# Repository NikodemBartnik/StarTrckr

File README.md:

## StarTracker - 3 axis astrophotography tracking solution

**Project is still in development and it may change!**<br>
Welcome to the StarTrckr project, an innovative solution to the problem of tracking in astrophotography. The goal of this project is to get over the limits of conventional tracking techniques so that hobbyists and enthusiasts can more easily take beautiful pictures of the night sky. Additionaly this construction enables for easier tracking of other objects (for example satellites) but the feature is not implemented yet.

A further benefit of the design is that it can be completely 3D printed, making it simple for everyone to construct and modify their own tracking device. It is planned to design an additional pro version that features steel parts for increased stiffness of the construction but 3D printed version will always stay as the bassis thats accesible and easy to replicate for everyone.

Since he was a young child, Nikodem Bartnik, the project's creator, has been fascinated about observing the night sky and space in general.  He is constantly searching for new ways to enhance the system and make it easier to use for users of all levels. At the same time he is into developing various open source projects and documenting the journeys of creating them on his YouTube channel. Additionaly is a part of Silesian Aerospace Technologies science club where together with friends he develops high altitude balloons, rockets and cubesat subsystems.

Designed by [Nikodem Bartnik](https://www.youtube.com/nikodembartnik). 

## Mechanics
Different design approaches have been considered and in the end multiple designs were created. Some of those are presented in the image below.

Most parts have been 3D printed and only a few additional parts like bearings, screws and motors are neccesary from the mechanical point of view. As of writing this readme there are three versions included in cad folder (v2, v3 nad v4). At this point v3 is prefered version and the one that is currently tested. Following list of printed parts reffers to v3.
| Name                | Amount |
|----------------------|-------|
| arm1.3mf             | 1     |
| arm2.3mf             | 1     |
| arm3.3mf             | 1     |
| base_pcb_box.3mf     | 1     |
| base_motor_holder.3mf| 1     |
| base_gear.3mf        | 1     |
| base_bearing_cap.3mf | 1     |
| base_gear_small.3mf  | 1     |
| gt2_pulley.3mf       | 2     |
| shaft.3mf            | 2     |
| shaft_cap.3mf        | 2     |
| bearing_flap.3mf     | 2     |
| quick_release_plate.3mf| 1   |
| quick_release1.3mf   | 1     |
| quick_release2.3mf   | 1     |
| pin.3mf              | 3     |

List of additional parts needed for the mechanical assembly:
| Name                | Amount | Description 
|----------------------|-------|-----------|
| Stepper motor 17HS08-1004S | 3     | Pancake type stepper motor, height: 20mm |
| 6205 bearing             | 2     | ball bearing |
| 6804 bearing             | 2     | ball bearing |
| GT2 belt 200mm          | 2     | 6mm wide    |
| GT2 pulley              | 2     | 16 teeth    |
| M6x60 screw             | 1     |  |
| M6 nut                  | 1     | |
| M5 screws               | a lot | lengths and amounts depend a lot on the version you are building |
| M5 nuts                 | a lot | |
| M3 screws               | a lot | lengths and amounts depend a lot on the version you are building |
| M3 nuts                 | a lot | |

## Electronics
In the pcb folder all files regarding electronics for the project can be found. Everything was designed with KiCad, there is the schematic and PCB layout together with zip archives with gerber files for production and schematic in png format. Here is a table with all components required to assemble the PCB.
| Name                | Amount | Description 
|----------------------|-------|-----------|
| RP2040              | 1     | Raspberry Pi microcontroller |
| A4988               | 3     | stepper driver, TMC2209 can be use as an upgrade to increase the accuracy |
| W25Q32JVSS          | 1     | Flash memory |
| USB socket          | 1     | type B |
| LM1117              | 1     | 3.3V linear voltage regulator |
| LED                 | 3     | size: 0805 preferably different color for each |
| Buzzer              | 1     | THT, 12mm |
| 12MHz crystal       | 1     | size: 5032 |
| 27 $\Omega$ resistor| 2     | size: 0603 |
| 100 $\Omega$ resistor|3    | size: 0603 |
| 1k $\Omega$ resistor | 2    | size: 0603 |
| 10k $\Omega$ resistor| 1    | size: 0603 |
| 27pF capacitor      | 2    | size: 0603 |
| 1uF capacitor       | 2    | size: 0603 |
| 10uF capacitor      | 3    | size: 0603 |
| 100nF capacitor     | 10   | size: 0603 |
| 2 pin screw terminal| 1    | |
| Some pin headers    |       | female and male, raster 2.54mm |

## Open Source
The StarTracker project is open-source, and the author welcomes feedback and contributions from the community. They believe that by sharing the project, they can help others to achieve the same level of success in capturing images of the night sky. If you are interested in building your own StarTrckr, the project's Github repository includes detailed instructions and all the necessary files to get started. Project was created as a bachelor thesis project at Silesian University of Technology and the created thesis can also be found in the repository as a PDF where one can read in depth about the research, problems and detailed explantion about the design process and decisions. 

## Software and firmware
Both were developed with Python programming language. As for now designed just as MVP to test basic functionality of the tractor will hopefully be developed more in the future.

## Testing
Example image untracked, f/5.6, ISO200, 600s, 55mm, Canon 600D after editing:

Example image with tracking enabled, same settings, camera and lens:

## Build Instruction
- todo 

## Project logo
<br>

<br><br>

## About the author
Since I was a young child, I have been fascinated about observing the night sky and space in general. I am into developing various open source projects and documenting the journeys of creating them on my YouTube channel. Additionaly I am a part of Silesian Aerospace Technologies science club where together with friends we develop high altitude balloons, rockets and cubesat subsystems.

I hope you enjoy using the StarTracker and are able to capture stunning images of the night sky with it. The StarTracker project is an ongoing effort, and I am always looking for ways to improve it. Feel free to contact me or contribute to the project if you have any ideas or suggestions. Together, we can make astrophotography more accessible and enjoyable for everyone!

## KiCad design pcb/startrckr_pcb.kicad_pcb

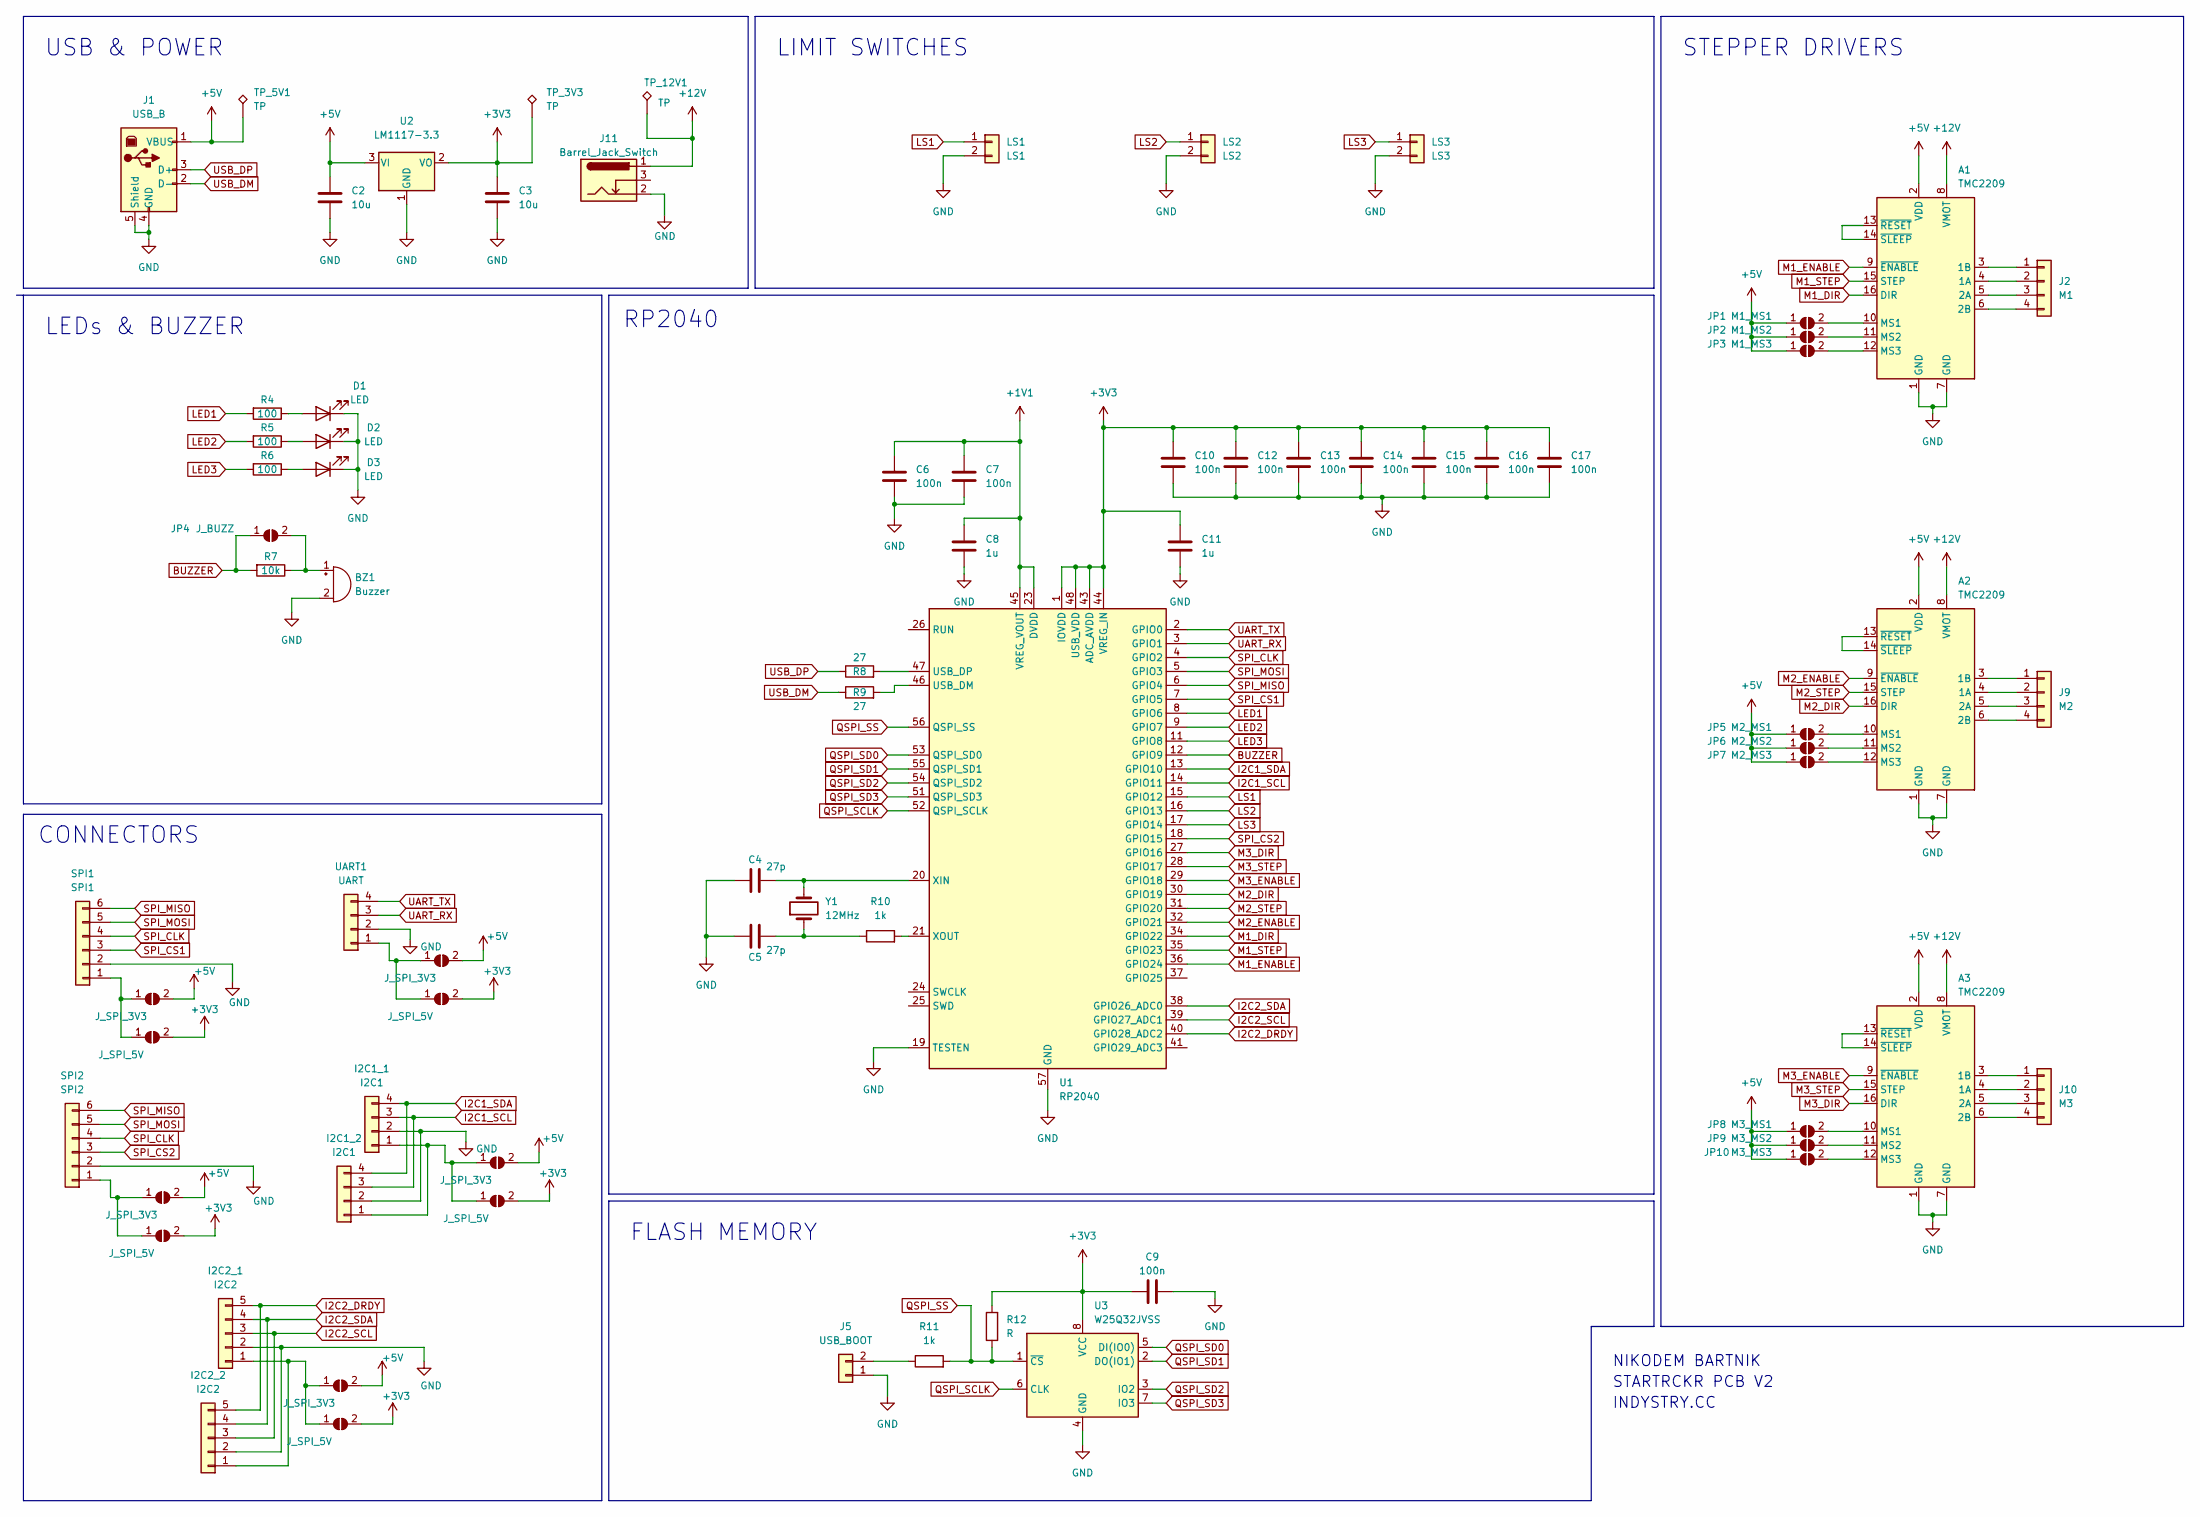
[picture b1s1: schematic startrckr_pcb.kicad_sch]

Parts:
A1, A2, A3: TMC2209; Pololu_Breakout-16_15.2x20.3mm
BZ1: Buzzer; Buzzer_12x9.5RM7.6
C2, C3: 10u; C_0603_1608Metric_Pad1.08x0.95mm_HandSolder
C4, C5: 27p; C_0603_1608Metric_Pad1.08x0.95mm_HandSolder
C6, C7, C9, C10, C12, C13, C14, C15, C16, C17: 100n; C_0603_1608Metric_Pad1.08x0.95mm_HandSolder
C8, C11: 1u; C_0603_1608Metric_Pad1.08x0.95mm_HandSolder
D1, D2, D3: LED; LED_0805_2012Metric_Pad1.15x1.40mm_HandSolder
I2C1_1, I2C1_2: I2C1; JST_XH_B4B-XH-A_1x04_P2.50mm_Vertical
I2C2_1, I2C2_2: I2C2; JST_XH_B5B-XH-A_1x05_P2.50mm_Vertical
J1: USB_B; U-USBBR04P-F000
J2: M1; JST_XH_B4B-XH-A_1x04_P2.50mm_Vertical
J5: USB_BOOT; PinHeader_1x02_P2.54mm_Vertical
J9: M2; JST_XH_B4B-XH-A_1x04_P2.50mm_Vertical
J10: M3; JST_XH_B4B-XH-A_1x04_P2.50mm_Vertical
J11: Barrel_Jack_Switch; BarrelJack_Horizontal
JP1: M1_MS1; SolderJumper-2_P1.3mm_Open_Pad1.0x1.5mm
JP2: M1_MS2; SolderJumper-2_P1.3mm_Open_Pad1.0x1.5mm
JP3: M1_MS3; SolderJumper-2_P1.3mm_Open_Pad1.0x1.5mm
JP4: J_BUZZ; SolderJumper-2_P1.3mm_Open_Pad1.0x1.5mm
JP5: M2_MS1; SolderJumper-2_P1.3mm_Open_Pad1.0x1.5mm
JP6: M2_MS2; SolderJumper-2_P1.3mm_Open_Pad1.0x1.5mm
JP7: M2_MS3; SolderJumper-2_P1.3mm_Open_Pad1.0x1.5mm
JP8: M3_MS1; SolderJumper-2_P1.3mm_Open_Pad1.0x1.5mm
JP9: M3_MS2; SolderJumper-2_P1.3mm_Open_Pad1.0x1.5mm
JP10: M3_MS3; SolderJumper-2_P1.3mm_Open_Pad1.0x1.5mm
JP11, JP13, JP15, JP17, JP19: J_SPI_3V3; SolderJumper-2_P1.3mm_Open_Pad1.0x1.5mm
JP12, JP14, JP16, JP18, JP20: J_SPI_5V; SolderJumper-2_P1.3mm_Open_Pad1.0x1.5mm
LS1: LS1; JST_XH_B2B-XH-A_1x02_P2.50mm_Vertical
LS2: LS2; JST_XH_B2B-XH-A_1x02_P2.50mm_Vertical
LS3: LS3; JST_XH_B2B-XH-A_1x02_P2.50mm_Vertical
R4, R5, R6: 100; R_0603_1608Metric_Pad0.98x0.95mm_HandSolder
R7: 10k; R_0603_1608Metric_Pad0.98x0.95mm_HandSolder
R8, R9: 27; R_0603_1608Metric_Pad0.98x0.95mm_HandSolder
R10, R11: 1k; R_0603_1608Metric_Pad0.98x0.95mm_HandSolder
R12: R; R_0603_1608Metric_Pad0.98x0.95mm_HandSolder
SPI1: SPI1; JST_XH_B6B-XH-A_1x06_P2.50mm_Vertical
SPI2: SPI2; JST_XH_B6B-XH-A_1x06_P2.50mm_Vertical
TP_3V3, TP_5V1, TP_12V1: TP; TestPoint_Pad_D1.5mm
U1: RP2040; QFN-56-1EP_7x7mm_P0.4mm_EP3.2x3.2mm
U2: LM1117-3.3; SOT-223-3_TabPin2
U3: W25Q32JVSS; SOIC-8_5.23x5.23mm_P1.27mm
UART1: UART; JST_XH_B4B-XH-A_1x04_P2.50mm_Vertical
Y1: 12MHz; Crystal_SMD_5032-2Pin_5.0x3.2mm

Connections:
+1V1: C6.1, C7.1, C8.1, U1.23 (DVDD), U1.45 (VREG_VOUT), U1.50 (DVDD)
+3V3: C3.1, C9.1, C10.1, C11.1, C12.1, C13.1, C14.1, C15.1, C16.1, C17.1, JP12.2 (B), JP14.2 (B), JP16.2 (B), JP18.2 (B), JP20.2 (B), R12.2, TP_3V3.1, U1.1 (IOVDD), U1.10 (IOVDD), U1.22 (IOVDD), U1.33 (IOVDD), U1.42 (IOVDD), U1.43 (ADC_AVDD), U1.44 (VREG_IN), U1.48 (USB_VDD), U1.49 (IOVDD), U2.2 (VO), U3.8 (VCC)
+5V: A1.2 (VDD), A2.2 (VDD), A3.2 (VDD), C2.1, J1.1 (VBUS), JP1.1 (A), JP2.1 (A), JP3.1 (A), JP5.1 (A), JP6.1 (A), JP7.1 (A), JP8.1 (A), JP9.1 (A), JP10.1 (A), JP11.2 (B), JP13.2 (B), JP15.2 (B), JP17.2 (B), JP19.2 (B), TP_5V1.1, U2.3 (VI)
+12V: A1.8 (VMOT), A2.8 (VMOT), A3.8 (VMOT), J11.1, TP_12V1.1
BUZZER: JP4.1 (A), R7.2, U1.12 (GPIO9)
GND: A1.1 (GND), A1.7 (GND), A2.1 (GND), A2.7 (GND), A3.1 (GND), A3.7 (GND), BZ1.2 (+), C2.2, C3.2, C4.1, C5.1, C6.2, C7.2, C8.2, C9.2, C10.2, C11.2, C12.2, C13.2, C14.2, C15.2, C16.2, C17.2, D1.1 (K), D2.1 (K), D3.1 (K), I2C1_1.2, I2C1_2.2, I2C2_1.2, I2C2_2.2, J1.4 (GND), J1.5 (Shield), J5.1, J11.2, LS1.2, LS2.2, LS3.2, SPI1.2, SPI2.2, U1.19 (TESTEN), U1.57 (GND), U2.1 (GND), U3.4 (GND), UART1.2
I2C1_SCL: I2C1_1.3, I2C1_2.3, U1.14 (GPIO11)
I2C1_SDA: I2C1_1.4, I2C1_2.4, U1.13 (GPIO10)
I2C2_DRDY: I2C2_1.5, I2C2_2.5, U1.40 (GPIO28_ADC2)
I2C2_SCL: I2C2_1.3, I2C2_2.3, U1.39 (GPIO27_ADC1)
I2C2_SDA: I2C2_1.4, I2C2_2.4, U1.38 (GPIO26_ADC0)
LED1: R4.2, U1.8 (GPIO6)
LED2: R5.2, U1.9 (GPIO7)
LED3: R6.2, U1.11 (GPIO8)
LS1: LS1.1, U1.15 (GPIO12)
LS2: LS2.1, U1.16 (GPIO13)
LS3: LS3.1, U1.17 (GPIO14)
M1_DIR: A1.16 (DIR), U1.34 (GPIO22)
M1_ENABLE: A1.9 (~ENABLE), U1.36 (GPIO24)
M1_STEP: A1.15 (STEP), U1.35 (GPIO23)
M2_DIR: A2.16 (DIR), U1.30 (GPIO19)
M2_ENABLE: A2.9 (~ENABLE), U1.32 (GPIO21)
M2_STEP: A2.15 (STEP), U1.31 (GPIO20)
M3_DIR: A3.16 (DIR), U1.27 (GPIO16)
M3_ENABLE: A3.9 (~ENABLE), U1.29 (GPIO18)
M3_STEP: A3.15 (STEP), U1.28 (GPIO17)
unnamed: A1.4 (1A), J2.2
unnamed: A1.3 (1B), J2.1
unnamed: A1.5 (2A), J2.3
unnamed: A1.6 (2B), J2.4
unnamed: A1.10 (MS1), JP1.2 (B)
unnamed: A1.11 (MS2), JP2.2 (B)
unnamed: A1.12 (MS3), JP3.2 (B)
unnamed: A1.13 (~RESET), A1.14 (~SLEEP)
unnamed: A2.4 (1A), J9.2
unnamed: A2.3 (1B), J9.1
unnamed: A2.5 (2A), J9.3
unnamed: A2.6 (2B), J9.4
unnamed: A2.10 (MS1), JP5.2 (B)
unnamed: A2.11 (MS2), JP6.2 (B)
unnamed: A2.12 (MS3), JP7.2 (B)
unnamed: A2.13 (~RESET), A2.14 (~SLEEP)
unnamed: A3.4 (1A), J10.2
unnamed: A3.3 (1B), J10.1
unnamed: A3.5 (2A), J10.3
unnamed: A3.6 (2B), J10.4
unnamed: A3.10 (MS1), JP8.2 (B)
unnamed: A3.11 (MS2), JP9.2 (B)
unnamed: A3.12 (MS3), JP10.2 (B)
unnamed: A3.13 (~RESET), A3.14 (~SLEEP)
unnamed: BZ1.1 (-), JP4.2 (B), R7.1
unnamed: C5.2, R10.1, Y1.1
unnamed: D1.2 (A), R4.1
unnamed: D2.2 (A), R5.1
unnamed: D3.2 (A), R6.1
unnamed: I2C1_1.1, I2C1_2.1, JP19.1 (A), JP20.1 (A)
unnamed: I2C2_1.1, I2C2_2.1, JP15.1 (A), JP16.1 (A)
unnamed: J5.2, R11.1
unnamed: JP11.1 (A), JP12.1 (A), SPI1.1
unnamed: JP13.1 (A), JP14.1 (A), SPI2.1
unnamed: JP17.1 (A), JP18.1 (A), UART1.1
unnamed: R9.2, U1.46 (USB_DM)
unnamed: R8.2, U1.47 (USB_DP)
unnamed: C4.2, U1.20 (XIN), Y1.2
unnamed: R10.2, U1.21 (XOUT)
QSPI_SCLK: U1.52 (QSPI_SCLK), U3.6 (CLK)
QSPI_SD0: U1.53 (QSPI_SD0), U3.5 (DI(IO0))
QSPI_SD1: U1.55 (QSPI_SD1), U3.2 (DO(IO1))
QSPI_SD2: U1.54 (QSPI_SD2), U3.3 (IO2)
QSPI_SD3: U1.51 (QSPI_SD3), U3.7 (IO3)
QSPI_SS: R11.2, R12.1, U1.56 (QSPI_SS), U3.1 (~CS)
SPI_CLK: SPI1.4, SPI2.4, U1.4 (GPIO2)
SPI_CS1: SPI1.3, U1.7 (GPIO5)
SPI_CS2: SPI2.3, U1.18 (GPIO15)
SPI_MISO: SPI1.6, SPI2.6, U1.6 (GPIO4)
SPI_MOSI: SPI1.5, SPI2.5, U1.5 (GPIO3)
UART_RX: U1.3 (GPIO1), UART1.3
UART_TX: U1.2 (GPIO0), UART1.4
USB_DM: J1.2 (D-), R9.1
USB_DP: J1.3 (D+), R8.1

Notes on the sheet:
STARTRCKR PCB V2
LIMIT SWITCHES
NIKODEM BARTNIK
INDYSTRY.CC
FLASH MEMORY
STEPPER DRIVERS
LEDs & BUZZER
USB & POWER
RP2040
CONNECTORS

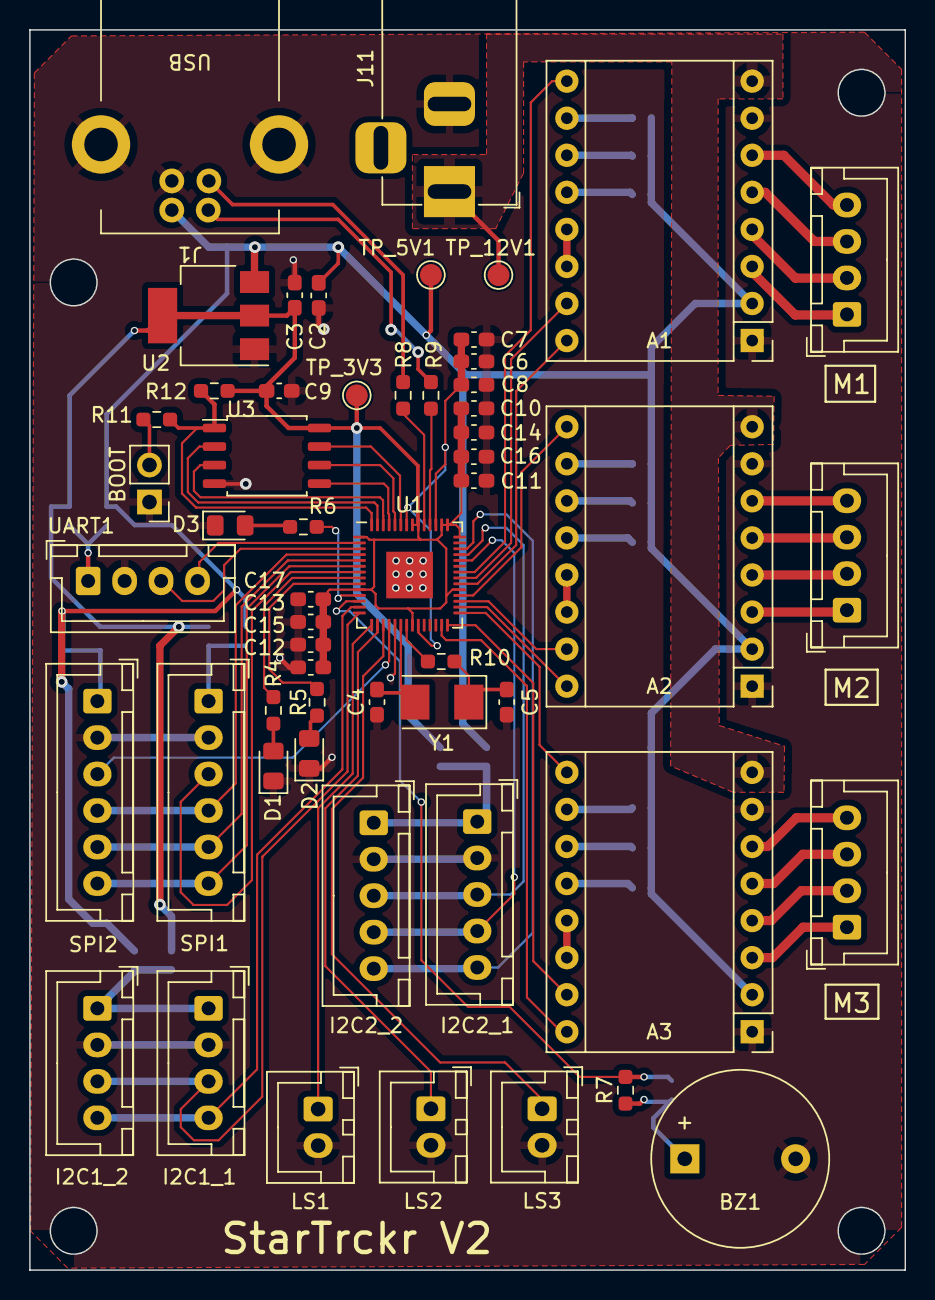
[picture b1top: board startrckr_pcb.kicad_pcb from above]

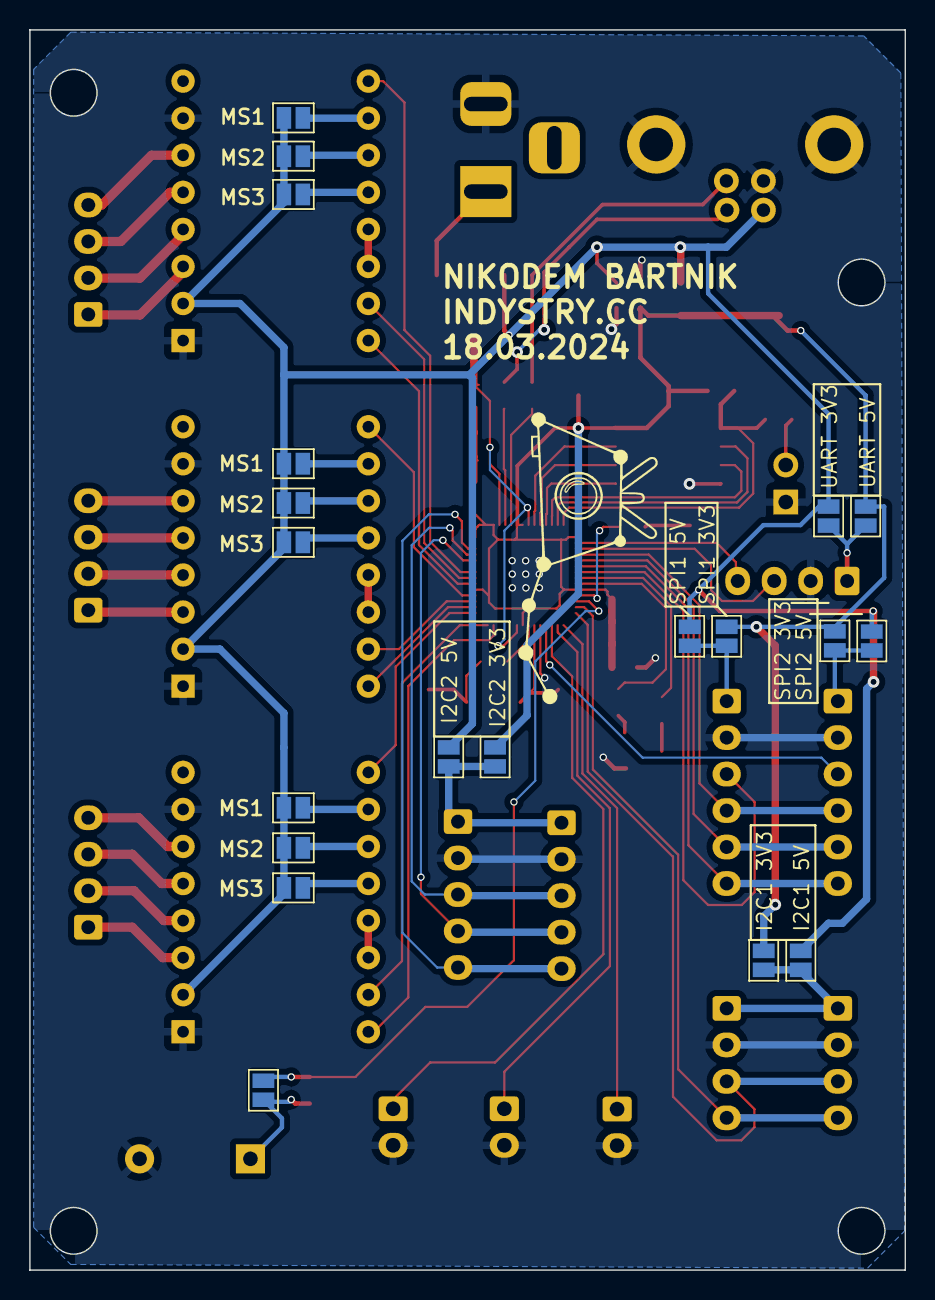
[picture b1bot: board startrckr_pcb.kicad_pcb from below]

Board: 2 copper layers, 60.0 x 85.0 mm, 75 parts (20 on the bottom side), 80 nets.

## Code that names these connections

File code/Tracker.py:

import time, sys
from machine import Pin, PWM
from StepperMotor import StepperMotor as Motor
from config import *


class Tracker:
    def __init__(self):
        self.led1 = Pin(PIN_LED_1, Pin.OUT)
        self.led2 = Pin(PIN_LED_2, Pin.OUT)
        self.led3 = Pin(PIN_LED_3, Pin.OUT)
        self.buzzer = PWM(Pin(PIN_BUZZER))
        self.buzzer.freq(3000)
        self.buzzer.duty_u16(0)

        self.ma = Motor(PIN_M1_ENABLE, PIN_M1_STEP, PIN_M1_DIR, M1_REVERSE_DIR)
        self.mb = Motor(PIN_M2_ENABLE, PIN_M2_STEP, PIN_M2_DIR, M2_REVERSE_DIR)
        self.mc = Motor(PIN_M3_ENABLE, PIN_M3_STEP, PIN_M3_DIR, M3_REVERSE_DIR)
        self.ma.enable()
        self.mb.enable()
        self.mc.enable()
        
        self.pos_a = 0
        self.pos_b = 0
        self.pos_c = 0
        
    def moveTo(self, dest_a, dest_b, dest_c):
        self.bresenham3D(dest_a, dest_b, dest_c)
        
        
    def bresenham3D(self, dest_a, dest_b, dest_c):
        da = abs(dest_a - self.pos_a)
        db = abs(dest_b - self.pos_b)
        dc = abs(dest_c - self.pos_c)
        
        print('da: ', da, 'db: ', db, 'dc: ', dc)
        
        dir_a = 1 if dest_a > self.pos_a else -1
        dir_b = 1 if dest_b > self.pos_b else -1
        dir_c = 1 if dest_c > self.pos_c else -1
        print('dira: ', dir_a, ' dirb: ', dir_b, ' dirc: ', dir_c)
        
        temp_a = 0
        temp_b = 0
        temp_c = 0
        if not (da == 0 and db == 0 and dc == 0):
            if da >= db and da >= dc:
                step_b = db / da
                step_c = dc / da

                for x in range(int(da)):
                    self.pos_a = self.pos_a + dir_a
                    self.ma.step(dir_a)
                    temp_b = temp_b + step_b
                    temp_c = temp_c + step_c
                    
                    if temp_b >= 1:
                        temp_b = temp_b - 1
                        self.pos_b = self.pos_b + dir_b
                        self.mb.step(dir_b)

                    if temp_c >= 1:
                        temp_c = temp_c - 1
                        self.pos_c = self.pos_c + dir_c
                        self.mc.step(dir_c)
                    time.sleep(DELAY_BETWEEN_STEPS)
                    #print(self.pos_a, self.pos_b, self.pos_c)
                    
            elif db >= da and db >= dc:
                step_a = da / db
                step_c = dc / db

                for x in range(int(db)):
                    self.pos_b = self.pos_b + dir_b
                    self.mb.step(dir_b)
                    temp_a = temp_a + step_a
                    temp_c = temp_c + step_c
                    
                    if temp_a >= 1:
                        temp_a = temp_a - 1
                        self.pos_a = self.pos_a + dir_a
                        self.ma.step(dir_a)

                    if temp_c >= 1:
                        temp_c = temp_c - 1
                        self.pos_c = self.pos_c + dir_c
                        self.mc.step(dir_c)
                    time.sleep(DELAY_BETWEEN_STEPS)
                    print(self.pos_a, self.pos_b, self.pos_c)

            elif dc >= da and dc >= db:
                step_a = da / dc
                step_b = db / dc

                for x in range(int(dc)):
                    self.pos_c = self.pos_c + dir_c
                    self.mc.step(dir_c)
                    temp_a = temp_a + step_a
                    temp_b = temp_b + step_b
                    
                    if temp_a >= 1:
                        temp_a = temp_a - 1
                        self.pos_a = self.pos_a + dir_a
                        self.ma.step(dir_a)

                    if temp_b >= 1:
                        temp_b = temp_b - 1
                        self.pos_b = self.pos_b + dir_b
                        self.mb.step(dir_b)
                    time.sleep(DELAY_BETWEEN_STEPS)
                    print(self.pos_a, self.pos_b, self.pos_c)
                
    def getA(self):
        return self.pos_a
    
    def getB(self):
        return self.pos_b
    
    def getC(self):
        return self.pos_c
                
                
    def buzzerSound():
        buzzer.duty_u16(30000)
        time.sleep(0.1)
        buzzer.duty_u16(0)
        time.sleep(0.5)
        buzzer.duty_u16(30000)
        time.sleep(0.1)
        buzzer.duty_u16(0)
        time.sleep(0.5)
        buzzer.duty_u16(30000)
        time.sleep(0.1)
        buzzer.duty_u16(0)
        time.sleep(3)

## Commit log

2022-10-26 pdf added to research
2022-11-05 values update
2022-11-29 added test.py with matrices operations
2022-11-29 add pcb step file
2022-11-29 added code and controller software
2022-11-29 created bresenham 3D algorithm
2022-11-29 extended bresenham3d algorithm and serial control
2022-11-30 bresenham 3d fixed
2022-11-30 step direction fixed
2022-11-30 added Tracker and config
    Main distributed to separate classes, better code structure and organisation. Config file created. Clean up
2022-11-30 changed ints to floats
2022-11-30 added math functions and serial control
2022-12-18 Update experiments
2022-12-20 update values in config
2022-12-20 3D plot for visualization
2022-12-22 v4 added, v2 started
2022-12-22 movement algorithms fix
2022-12-25 rotation matrix fix, clean up
2022-12-25 algorithm fix
2022-12-25 working algorithm! (most likely)
2022-12-28 GUI development, new features
2023-01-02 Altitude rotation fix
2023-01-02 added dire reverse
2023-01-03 added schematic.png
2023-01-03 changed decimalToDms to a private method
2023-01-03 added CAD files
2023-01-04 euler angles experiment
2023-01-04 partial fix
2023-01-04 angle calculation fix
2023-01-04 cleanup
2023-01-04 remove pcb backups
2023-01-11 readme update
2023-01-11 clean up
2023-01-11 cad update
2023-04-23 documents uploaded to APD added
2023-04-23 fix wrong sign in tracking algorithm
2023-07-18 clean up + power jack
2023-10-26 add basic image processing
2023-10-26 detecting and highlighting the biggest stars
2024-03-18 Schematic update
2024-03-18 PCB V2 ready
2024-05-21 test
2024-05-21 new functions for RA-dec calculation
2024-05-21 add function to convert ALT-AZ to RA-DEC
2024-05-21 working alt-az to ra-dec
2024-05-22 display ra dec coordinates in GUI
2024-05-22 rotation matrix formula fix
2024-09-16 add logo files
2024-09-16 add more images/docs
2024-09-16 add images
